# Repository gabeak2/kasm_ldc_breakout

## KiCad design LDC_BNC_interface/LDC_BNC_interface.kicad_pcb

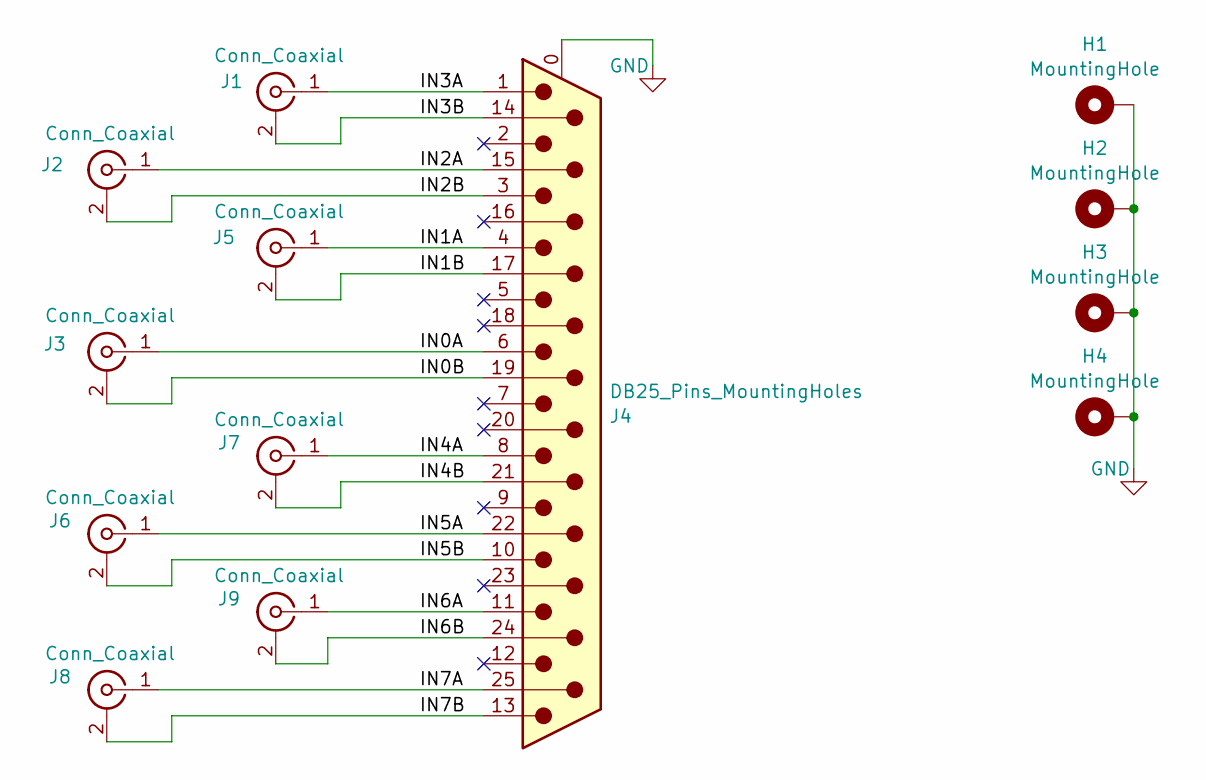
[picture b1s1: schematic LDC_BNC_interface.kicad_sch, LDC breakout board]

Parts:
H1, H2, H3, H4: MountingHole; MountingHole_3.2mm_M3_DIN965_Pad
J1, J2, J3, J5, J6, J7, J8, J9: Conn_Coaxial; KH-BNC50-3511; LCSC C2837587
J4: DB25_Pins_MountingHoles; TE-5747842-4; LCSC C305948

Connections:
/IN0A: J3.1 (In), J4.6
/IN0B: J3.2 (Ext), J4.19
/IN1A: J4.4, J5.1 (In)
/IN1B: J4.17, J5.2 (Ext)
/IN2A: J2.1 (In), J4.15
/IN2B: J2.2 (Ext), J4.3
/IN3A: J1.1 (In), J4.1
/IN3B: J1.2 (Ext), J4.14
/IN4A: J4.8, J7.1 (In)
/IN4B: J4.21, J7.2 (Ext)
/IN5A: J4.22, J6.1 (In)
/IN5B: J4.10, J6.2 (Ext)
/IN6A: J4.11, J9.1 (In)
/IN6B: J4.24, J9.2 (Ext)
/IN7A: J4.25, J8.1 (In)
/IN7B: J4.13, J8.2 (Ext)
GND: H1.1, H2.1, H3.1, H4.1, J4.0 (PAD)

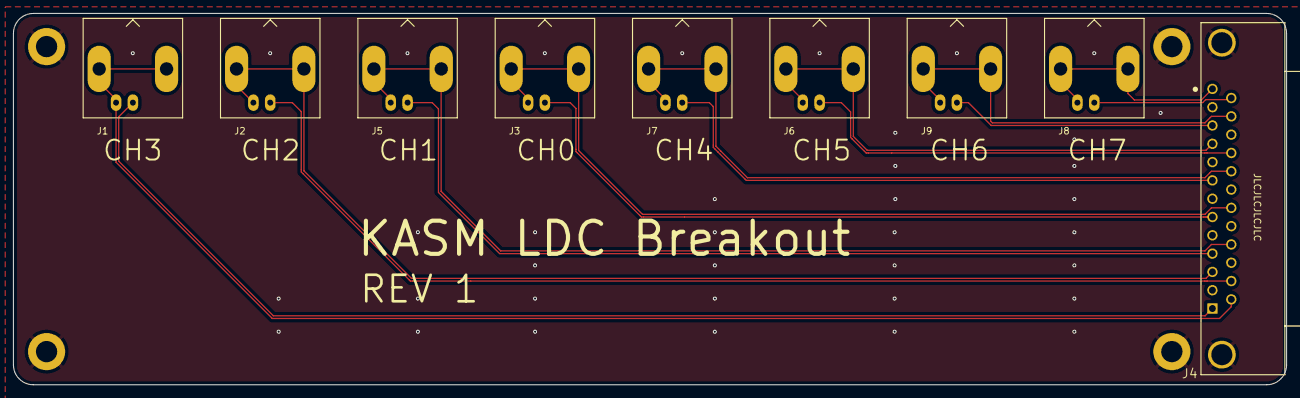
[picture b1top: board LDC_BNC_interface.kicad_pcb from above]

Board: 2 copper layers, 192.0 x 56.0 mm, 13 parts (0 on the bottom side), 17 nets.

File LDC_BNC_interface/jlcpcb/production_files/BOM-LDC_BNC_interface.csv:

Comment,Designator,Footprint,LCSC,Quantity
Conn_Coaxial,"J1,J2,J3,J5,J6,J7,J8,J9",KH-BNC50-3511,C2837587,8
DB25_Pins_MountingHoles,J4,TE-5747842-4,C305948,1

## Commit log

2025-06-08 Widened PCB
